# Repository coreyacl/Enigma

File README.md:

# Enigma Visualization

#### A repository holding all code and PCB files regarding the Enigma visualization project for Fall 2018 Principles of Engineering course at Olin College of Engineering.

For more information on the project please go to [http://poe.olin.edu/2018/enigma](http://poe.olin.edu/2018/enigma)

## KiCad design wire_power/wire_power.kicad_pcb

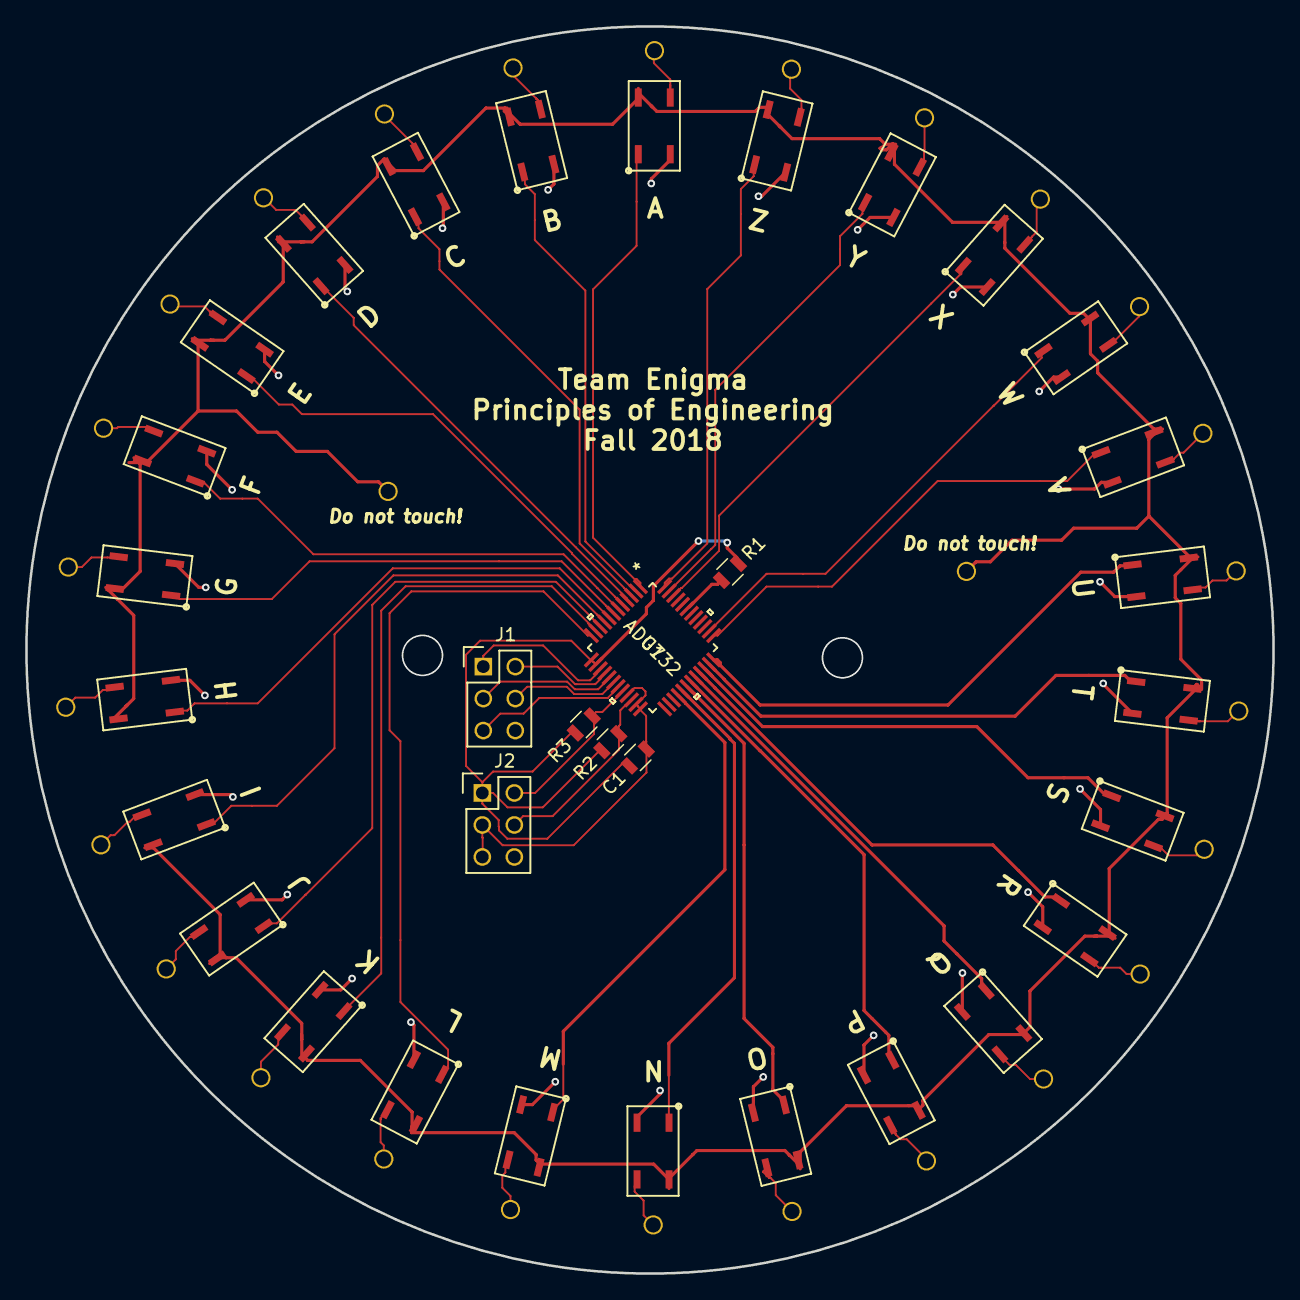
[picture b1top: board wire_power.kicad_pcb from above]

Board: 2 copper layers, 99.0 x 99.0 mm, 61 parts (0 on the bottom side), 63 nets.

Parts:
C1: C_0.1uF; R_0805_OEM
J1, J2: CONN_02X03; Pin_Header_Straight_2x03
J3, J4, J5, J6, J7, J8, J9, J10, J11, J12, J13, J14, J15, J16, J17, J18, J19, J20, J21, J22, J23, J24, J25, J26, J27, J28, J29, J30: Through_hole; thru_hole
Q1, Q2, Q3, Q4, Q5, Q6, Q7, Q8, Q9, Q10, Q11, Q12, Q13, Q14, Q15, Q16, Q17, Q18, Q19, Q20, Q21, Q22, Q23, Q24, Q25, Q26: CPC1025NTR; relay
R1: R_200; R_0805_OEM
R2, R3: R_10K; R_0805_OEM
U1: ADG732; ADG732BSUZ-REEL

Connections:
/A0: J1.1, U1.15
/A1: J1.2, U1.16
/A2: J1.3, U1.17
/A3: J1.4, U1.18
/A4: J1.5, U1.19
/Hot_in: J3.1, J30.1, Q1.4, Q2.4, Q3.4, Q4.4, Q5.4, Q6.4, Q7.4, Q8.4, Q9.4, Q10.4, Q11.4, Q12.4, Q13.4, Q14.4, Q15.4, Q16.4, Q17.4, Q18.4, Q19.4, Q20.4, Q21.4, Q22.4, Q23.4, Q24.4, Q25.4, Q26.4
/Hot_outA: J4.1, Q1.3
/Hot_outB: J5.1, Q2.3
/Hot_outC: J6.1, Q3.3
/Hot_outD: J7.1, Q4.3
/Hot_outE: J8.1, Q5.3
/Hot_outF: J9.1, Q6.3
/Hot_outG: J10.1, Q7.3
/Hot_outH: J11.1, Q8.3
/Hot_outI: J12.1, Q9.3
/Hot_outJ: J13.1, Q10.3
/Hot_outK: J14.1, Q11.3
/Hot_outL: J15.1, Q12.3
/Hot_outM: J16.1, Q13.3
/Hot_outN: J17.1, Q14.3
/Hot_outO: J18.1, Q15.3
/Hot_outP: J19.1, Q16.3
/Hot_outQ: J20.1, Q17.3
/Hot_outR: J21.1, Q18.3
/Hot_outS: J22.1, Q19.3
/Hot_outT: J23.1, Q20.3
/Hot_outU: J24.1, Q21.3
/Hot_outV: J25.1, Q22.3
/Hot_outW: J26.1, Q23.3
/Hot_outX: J27.1, Q24.3
/Hot_outY: J28.1, Q25.3
/Hot_outZ: J29.1, Q26.3
/SA: Q1.1, U1.1
/SB: Q2.1, U1.2
/SC: Q3.1, U1.3
/SD: Q4.1, U1.4
/SE: Q5.1, U1.5
/SF: Q6.1, U1.6
/SG: Q7.1, U1.7
/SH: Q8.1, U1.8
/SI: Q9.1, U1.9
/SJ: Q10.1, U1.10
/SK: Q11.1, U1.11
/SL: Q12.1, U1.12
/SM: Q13.1, U1.28
/SN: Q14.1, U1.29
/SO: Q15.1, U1.30
/SP: Q16.1, U1.31
/SQ: Q17.1, U1.32
/SR: Q18.1, U1.33
/SS: Q19.1, U1.34
/ST: Q20.1, U1.35
/SU: Q21.1, U1.36
/SV: Q22.1, U1.37
/SW: Q23.1, U1.38
/SX: Q24.1, U1.46
/SY: Q25.1, U1.47
/SZ: Q26.1, U1.48
/~CS: J2.2, R3.2, U1.20
/~EN: J2.4, R2.2, U1.22
GND: C1.2, J2.3, J2.5, Q1.2, Q2.2, Q3.2, Q4.2, Q5.2, Q6.2, Q7.2, Q8.2, Q9.2, Q10.2, Q11.2, Q12.2, Q13.2, Q14.2, Q15.2, Q16.2, Q17.2, Q18.2, Q19.2, Q20.2, Q21.2, Q22.2, Q23.2, Q24.2, Q25.2, Q26.2, U1.21, U1.23, U1.24
unnamed: R1.2, U1.43
VCC: C1.1, J2.1, R1.1, R2.1, R3.1, U1.13, U1.14

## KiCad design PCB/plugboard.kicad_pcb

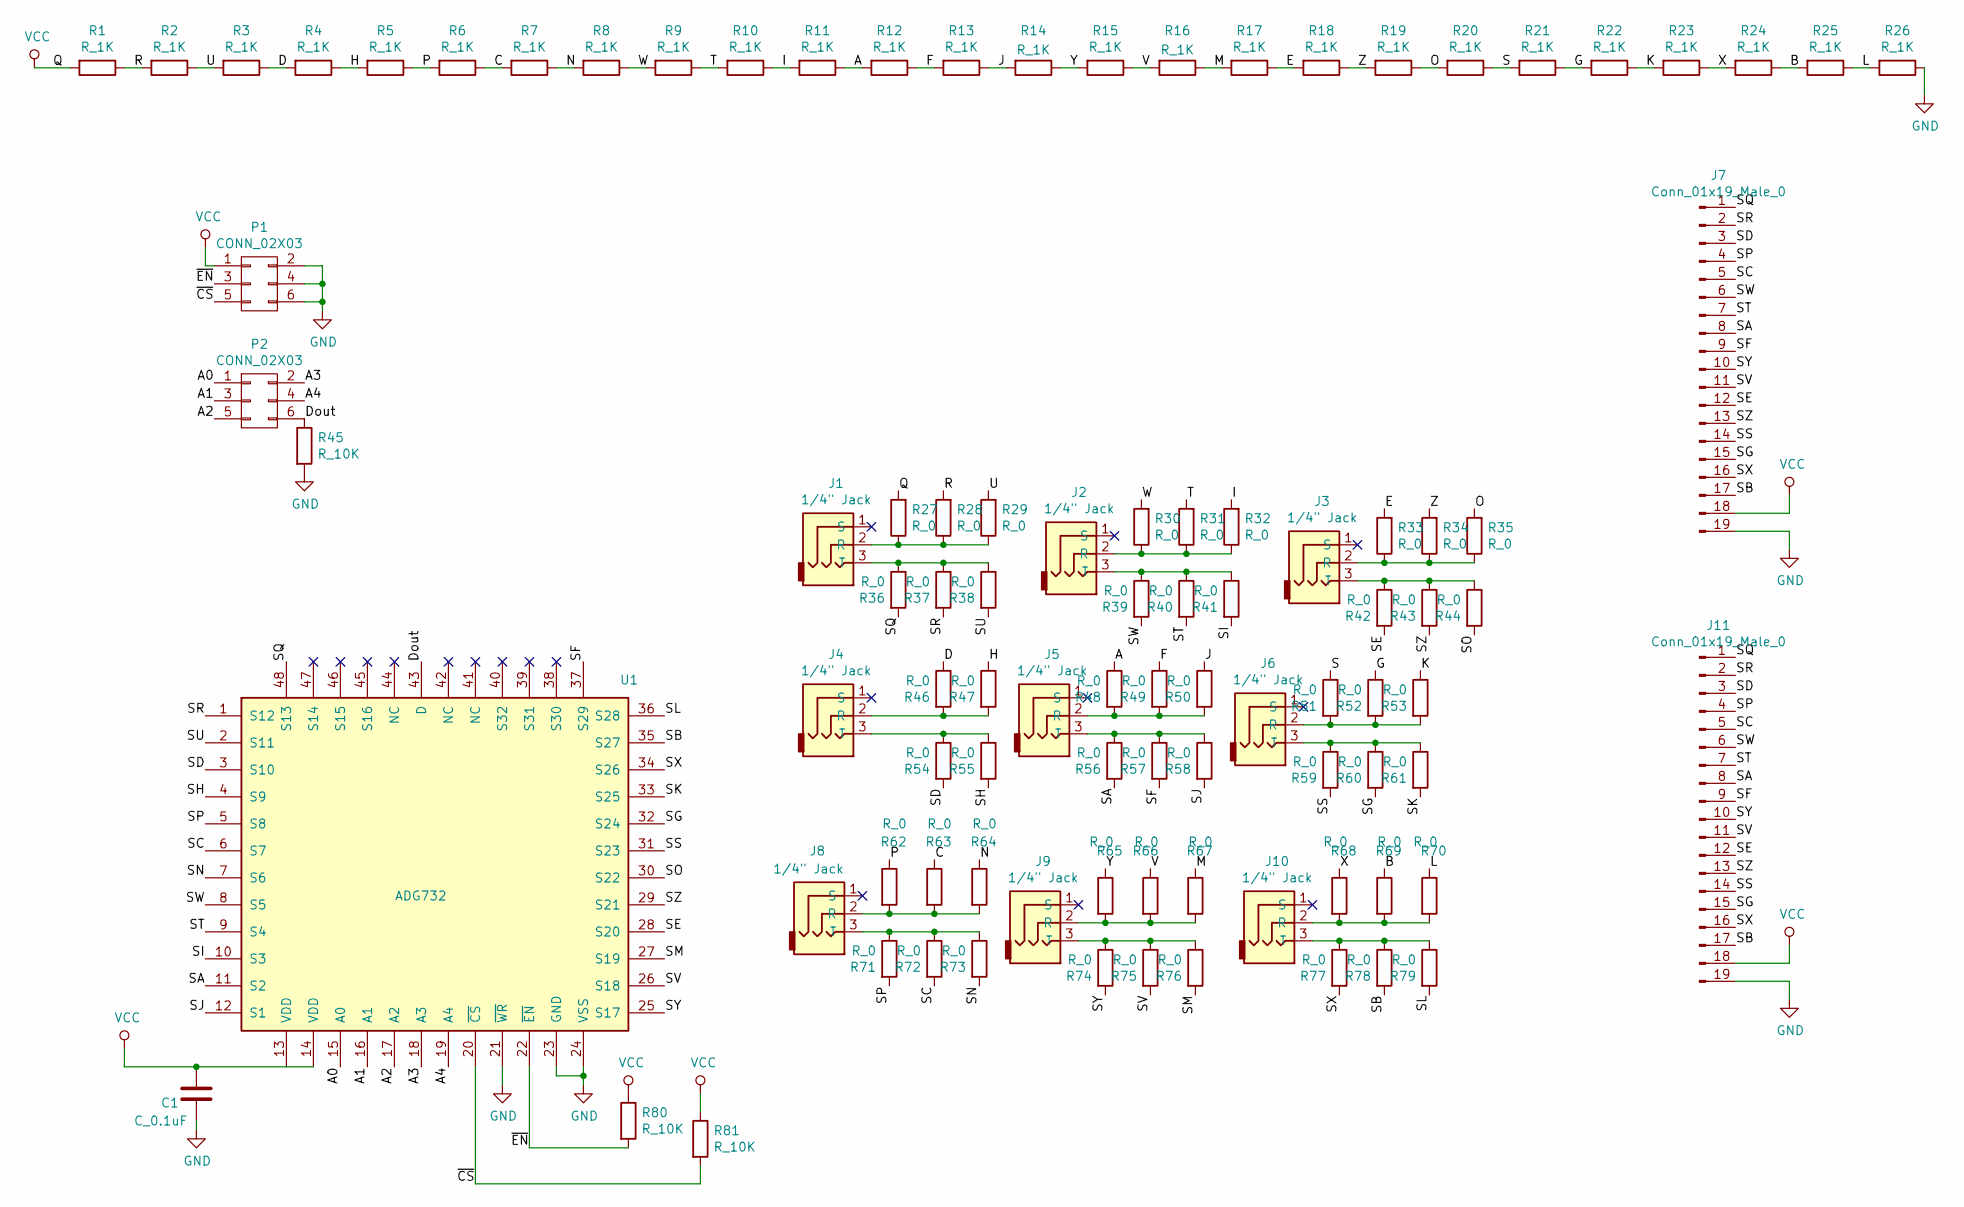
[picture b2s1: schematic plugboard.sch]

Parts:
C1: C_0.1uF; R_0805_OEM; MPN 478-3352-1-ND
J1, J2, J3, J4, J5, J6, J8, J9, J10: 1/4\" Jack; jack_hole; MPN 112BX
J7, J11: Conn_01x19_Male_0; sidebar
P1, P2: CONN_02X03; Pin_Header_Straight_2x03; MPN 609-3234-ND
R1, R2, R3, R4, R5, R6, R7, R8, R9, R10, R11, R12, R13, R14, R15, R16, R17, R18, R19, R20, R21, R22, R23, R24, R25, R26: R_1K; R_0805_OEM; MPN RNCP0805FTD1K00CT-ND
R27, R28, R29, R30, R31, R32, R33, R34, R35, R36, R37, R38, R39, R40, R41, R42, R43, R44, R46, R47, R48, R49, R50, R51, R52, R53, R54, R55, R56, R57, R58, R59, R60, R61, R62, R63, R64, R65, R66, R67, R68, R69, R70, R71, R72, R73, R74, R75, R76, R77, R78, R79: R_0; R_0805_OEM
R45, R80, R81: R_10K; R_0805_OEM; MPN CRS0805-FX-1002ELFCT-ND
U1: ADG732; ADG732BSUZ-REEL; MPN ADG732BSUZ-REEL

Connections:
/A: R11.1, R12.2, R48.1
/A0: P2.1, U1.15 (A0)
/A1: P2.3, U1.16 (A1)
/A2: P2.5, U1.17 (A2)
/A3: P2.2, U1.18 (A3)
/A4: P2.4, U1.19 (A4)
/B: R24.1, R25.2, R69.1
/C: R6.1, R7.2, R63.1
/D: R3.1, R4.2, R46.1
/Dout: P2.6, R45.1, U1.43 (D)
/E: R17.1, R18.2, R33.2
/F: R12.1, R13.2, R49.1
/G: R21.1, R22.2, R52.1
/H: R4.1, R5.2, R47.1
/I: R10.1, R11.2, R32.2
/J: R13.1, R14.2, R50.1
/K: R22.1, R23.2, R53.1
/L: R25.1, R26.2, R70.1
/M: R16.1, R17.2, R67.1
/N: R7.1, R8.2, R64.1
/O: R19.1, R20.2, R35.2
/P: R5.1, R6.2, R62.1
/R: R1.1, R2.2, R28.2
/S: R20.1, R21.2, R51.1
/SA: J7.8, J11.8, R56.2, U1.11 (S2)
/SB: J7.17, J11.17, R78.2, U1.35 (S27)
/SC: J7.5, J11.5, R72.2, U1.6 (S7)
/SD: J7.3, J11.3, R54.2, U1.3 (S10)
/SE: J7.12, J11.12, R42.2, U1.28 (S20)
/SF: J7.9, J11.9, R57.2, U1.37 (S29)
/SG: J7.15, J11.15, R60.2, U1.32 (S24)
/SH: R55.2, U1.4 (S9)
/SI: R41.2, U1.10 (S3)
/SJ: R58.2, U1.12 (S1)
/SK: R61.2, U1.33 (S25)
/SL: R79.2, U1.36 (S28)
/SM: R76.2, U1.27 (S19)
/SN: R73.2, U1.7 (S6)
/SO: R44.2, U1.30 (S22)
/SP: J7.4, J11.4, R71.2, U1.5 (S8)
/SQ: J7.1, J11.1, R36.2, U1.48 (S13)
/SR: J7.2, J11.2, R37.2, U1.1 (S12)
/SS: J7.14, J11.14, R59.2, U1.31 (S23)
/ST: J7.7, J11.7, R40.2, U1.9 (S4)
/SU: R38.2, U1.2 (S11)
/SV: J7.11, J11.11, R75.2, U1.26 (S18)
/SW: J7.6, J11.6, R39.2, U1.8 (S5)
/SX: J7.16, J11.16, R77.2, U1.34 (S26)
/SY: J7.10, J11.10, R74.2, U1.25 (S17)
/SZ: J7.13, J11.13, R43.2, U1.29 (S21)
/T: R9.1, R10.2, R31.2
/U: R2.1, R3.2, R29.2
/V: R15.1, R16.2, R66.1
/W: R8.1, R9.2, R30.2
/X: R23.1, R24.2, R68.1
/Y: R14.1, R15.2, R65.1
/Z: R18.1, R19.2, R34.2
/~CS: P1.5, R81.2, U1.20 (~CS)
/~EN: P1.3, R80.2, U1.22 (~EN)
GND: C1.2, J7.19, J11.19, P1.2, P1.4, P1.6, R26.1, R45.2, U1.21 (~WR), U1.23 (GND), U1.24 (VSS)
unnamed: J1.2 (R), R27.1, R28.1, R29.1
unnamed: J1.3 (T), R36.1, R37.1, R38.1
unnamed: J2.2 (R), R30.1, R31.1, R32.1
unnamed: J2.3 (T), R39.1, R40.1, R41.1
unnamed: J3.2 (R), R33.1, R34.1, R35.1
unnamed: J3.3 (T), R42.1, R43.1, R44.1
unnamed: J4.2 (R), R46.2, R47.2
unnamed: J4.3 (T), R54.1, R55.1
unnamed: J5.2 (R), R48.2, R49.2, R50.2
unnamed: J5.3 (T), R56.1, R57.1, R58.1
unnamed: J6.2 (R), R51.2, R52.2, R53.2
unnamed: J6.3 (T), R59.1, R60.1, R61.1
unnamed: J8.2 (R), R62.2, R63.2, R64.2
unnamed: J8.3 (T), R71.1, R72.1, R73.1
unnamed: J9.2 (R), R65.2, R66.2, R67.2
unnamed: J9.3 (T), R74.1, R75.1, R76.1
unnamed: J10.2 (R), R68.2, R69.2, R70.2
unnamed: J10.3 (T), R77.1, R78.1, R79.1
VCC: C1.1, J7.18, J11.18, P1.1, R1.2, R27.2, R80.1, R81.1, U1.14 (VDD)

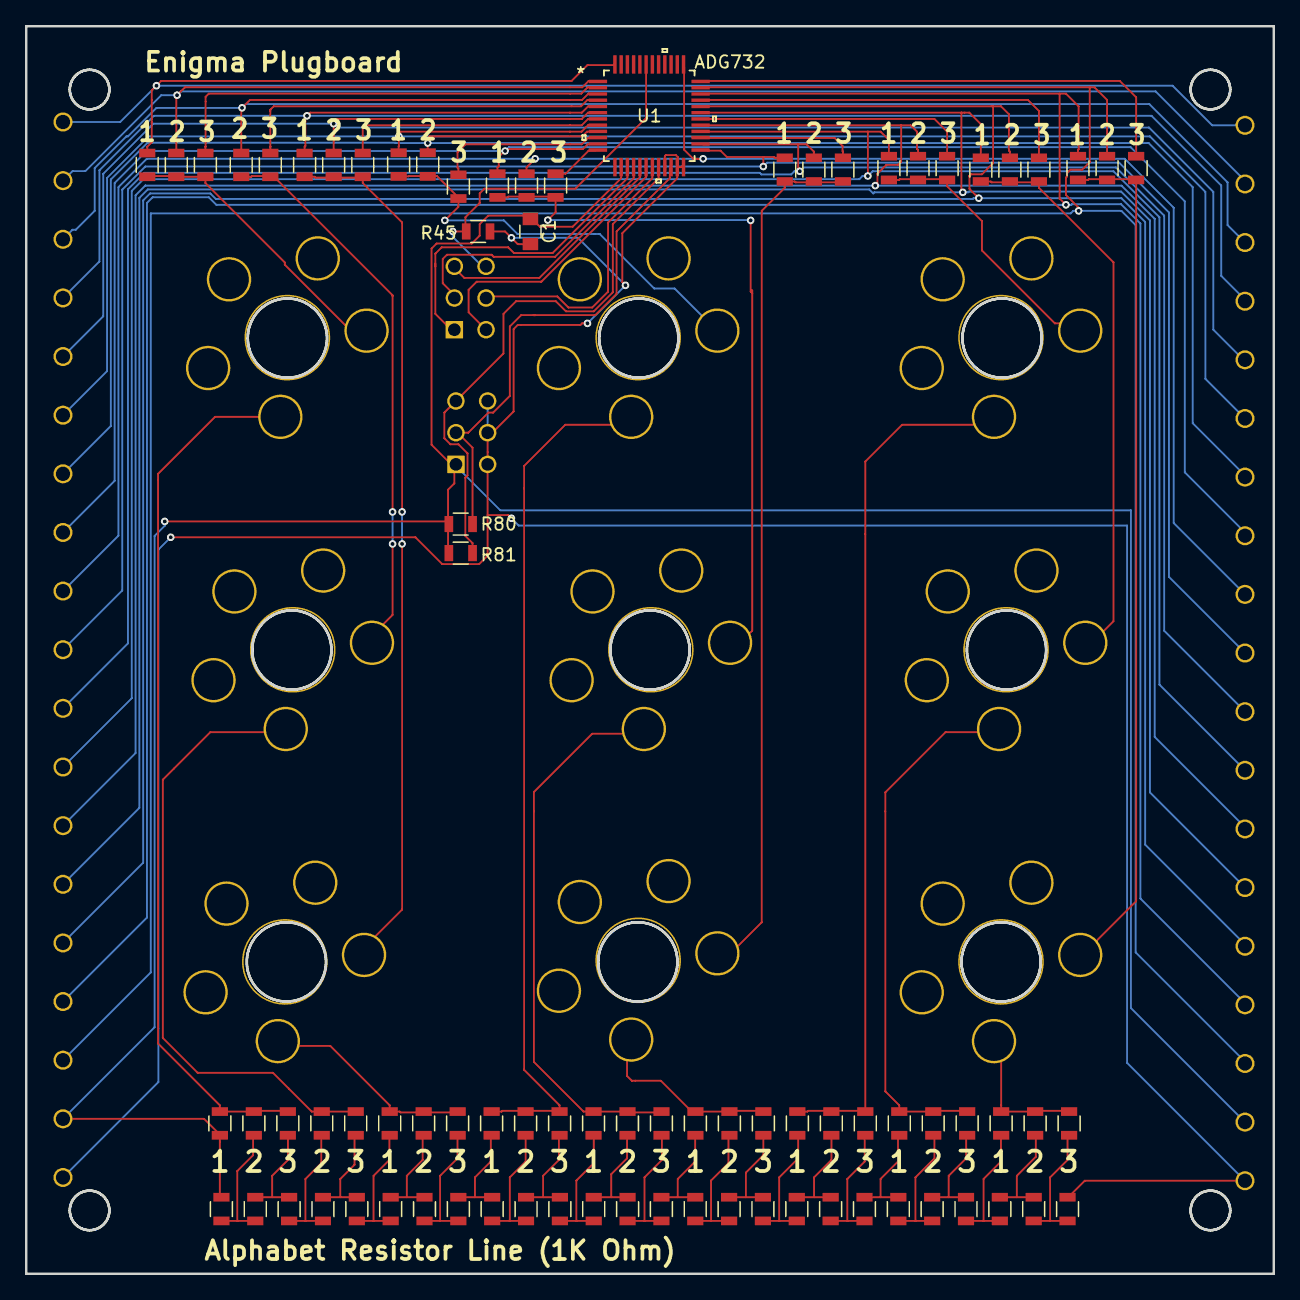
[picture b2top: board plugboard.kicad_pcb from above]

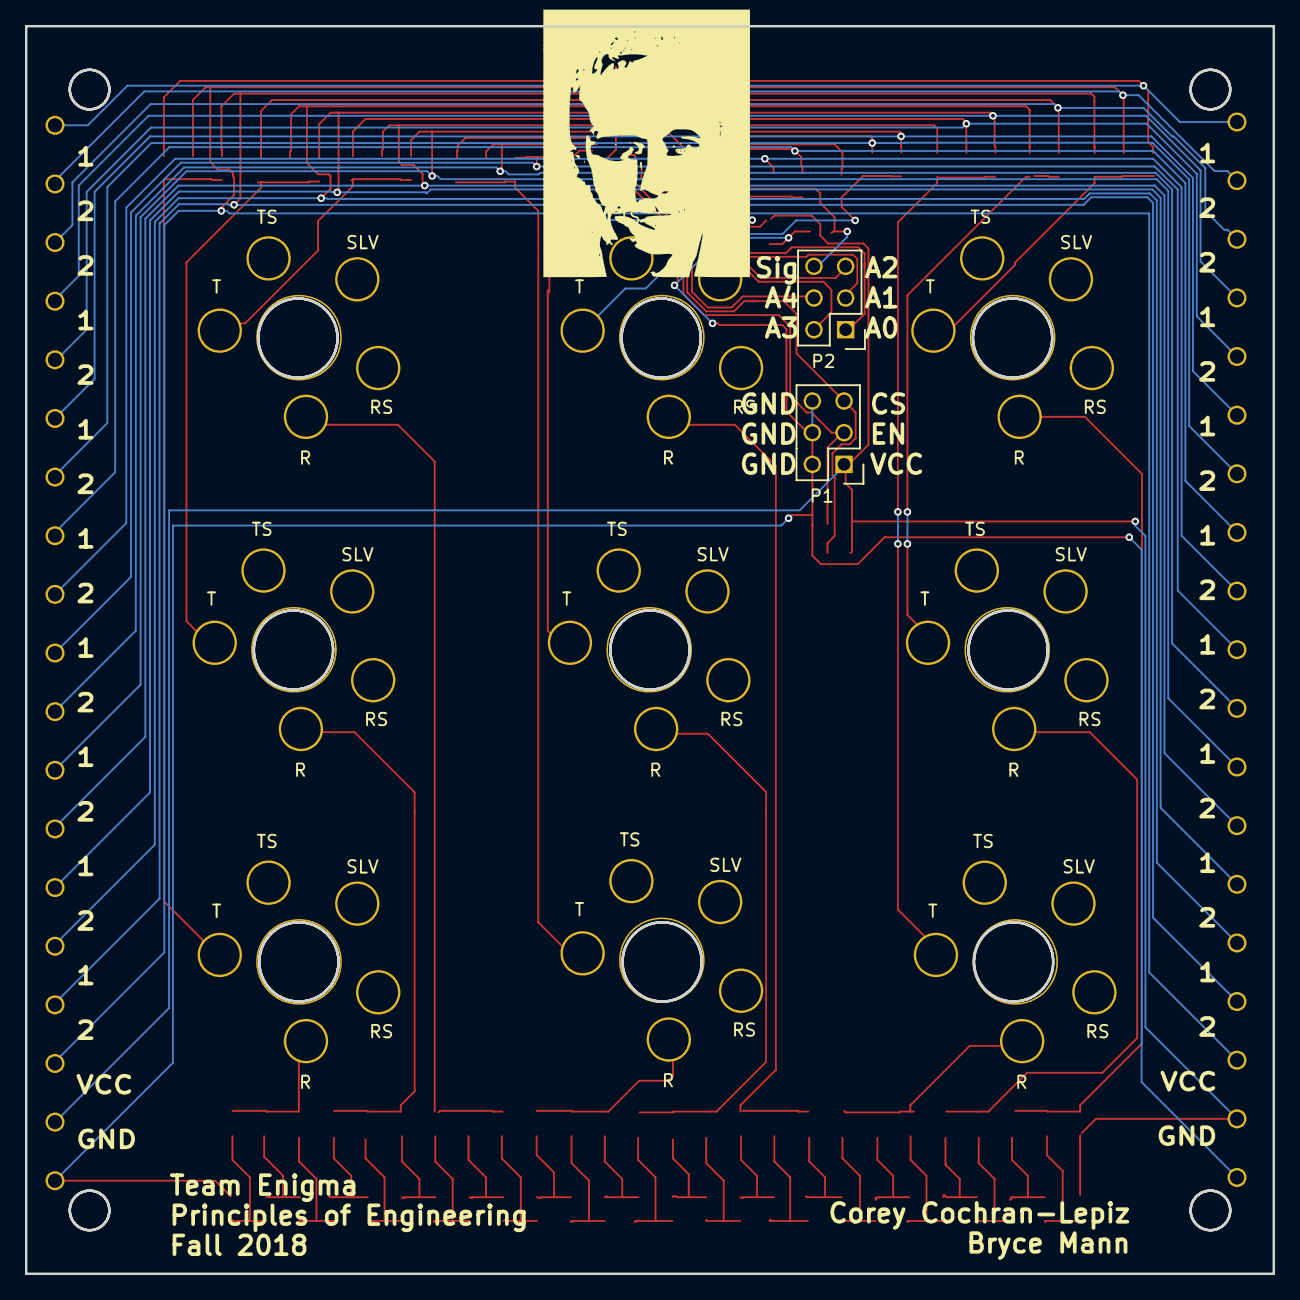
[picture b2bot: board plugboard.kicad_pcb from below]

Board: 2 copper layers, 100.0 x 100.0 mm, 96 parts (2 on the bottom side), 79 nets.

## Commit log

2018-11-05 add .gitignore
2018-11-05 Add footprints library
2018-11-05 added pull down resistors
2018-11-06 Add jack and bar parts
2018-11-06 fix placement of jack on schemtaic
2018-11-06 Part for the plugboard for aesthetic.
2018-11-06 Slightly improved version of the jack heads places
2018-11-06 Basic Layout
    Now I'm gonna start on tracing.
2018-11-06 update schematic
    I'm gonna try something...
2018-11-06 More Layout
    I think it's working...
2018-11-06 Layout work
    It's working!
    I did a few optimization changes to make layout smoother.
    Changed around the netlist essentially
2018-11-07 Finish first draft layout
2018-11-07 checked layout, cleaned up a few traces
2018-11-12 Final rev
2018-11-12 Adding screen caps
2018-11-13 made project for the board that will power the wire
2018-11-14 first powerboard sch
2018-11-15 Bryce pull request
2018-11-15 Updates letter labelling relays
2018-11-15 Fix schematic
2018-11-15 swapping R/T instead of S/T
2018-11-16 Final plugboard
    Added a bit more tolerance on the jack_hole footprint
    Fix layout to accomodate for tip ring usage
    Made silkscreen a bit more clear
2018-11-16 Add GERBER files
    Add GERBER files for plugboard
    Add new footprint for TLP785(LF6) relay for power board
2018-11-26 First pass at wire_power layout UNFINISHED
    laid everyhing out in a circle
    routed all the MUX ins and outs
    Still need to place the input for HOT
    Still need to route GND traces
2018-11-26 final pass at wire_power layout)
2018-11-26 Revised final pass of wire_power layout
2018-12-02 Add code and zip
    Started arduino code for the plugboard. At this point it just runs through all of the MUX channels and prints out the values.
    Added gerber files for the power board
2018-12-06 Update code
    added a few functions to handle power board
    setup lists for both MUXs
    voltage line list
2018-12-26 Modify README

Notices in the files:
parts and their libraries:
Copyright 2016 Accelerated Designs. All rights reserved.
